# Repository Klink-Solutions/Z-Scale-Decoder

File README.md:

# Z-Scale-Decoder

### A ultra tiny DCC decoder build for Z scale trains using the universal DCC protocoll at 10V

## Why this exists
All Z-scale trains on the market today are analog meaning they have poor slow speed performance as the motor jolts to life to get it going. They are also limited to only 1 train per track loop.
My DCC decoder is meant to bridge this gap and fit in larger locomotives and the Rokuhan® "Shorties" carriages to allow for precise pwm motor control with back EMF detection, multiple trains per loop, and optional rgb LED for dynamic running lights.  

## What it does

* ATtiny826 8-bit AVR MCU base running a DCC decoder
* Runs straight from DCC track power, up to 10 V
* Bridge rectifier, (So it works with either track polarity)
* DRV8220 H-bridge motor driver for high compatibility
* Back-EMF speed regulation 
* Optional directional front and rear lights plus an optional cab light
* TPS70950 5 V LDO 
* UPDI programming pads  
* 12 x 7.5 mm
* 2-layer board,0201 componets

## Version History
* 0.1
    * Initial release 

## BOM
|Value         |Designator |Footprint     |JLCPCB Part #          |
|--------------|-----------|--------------|-----------------------|
|0.1uF         |C1,C3      |C0201         |C2158829               |
|10uF 25V      |C2         |C1206         |C2158829               |
|2.2uF         |C4         |C0201         |C6204143               |
|1uF           |C5         |C0201         |C307385                |
|PMEG3010AESBYL|D1,D2,D3,D4|D0402         |C28646369              |
|220k          |R1         |R0201         |C158699                |
|470           |R2         |R0201         |C144816                |
|47k           |R3,R5      |R0201         |C100140                |
|22k           |R4,R6      |R0201         |C295842                |
|DRV8220DSGR   |U1         |WSON-8(2x2)   |C3681269               |
|TPS70950DRVR  |U2         |WSON-6-EP(2x2)|C527527                |
|ATTINY826-MU  |U3         |VQFN-20(3x3)  |C3216887               |

## Help

Contact author 

## Author

Lucas Klemmer  
klinksolutions22@gmail.com

## License
MIT LIcense

If anyone ends up reproducing this device or making it even bettter I would be happy to see your improvements and add them to the oficial release.

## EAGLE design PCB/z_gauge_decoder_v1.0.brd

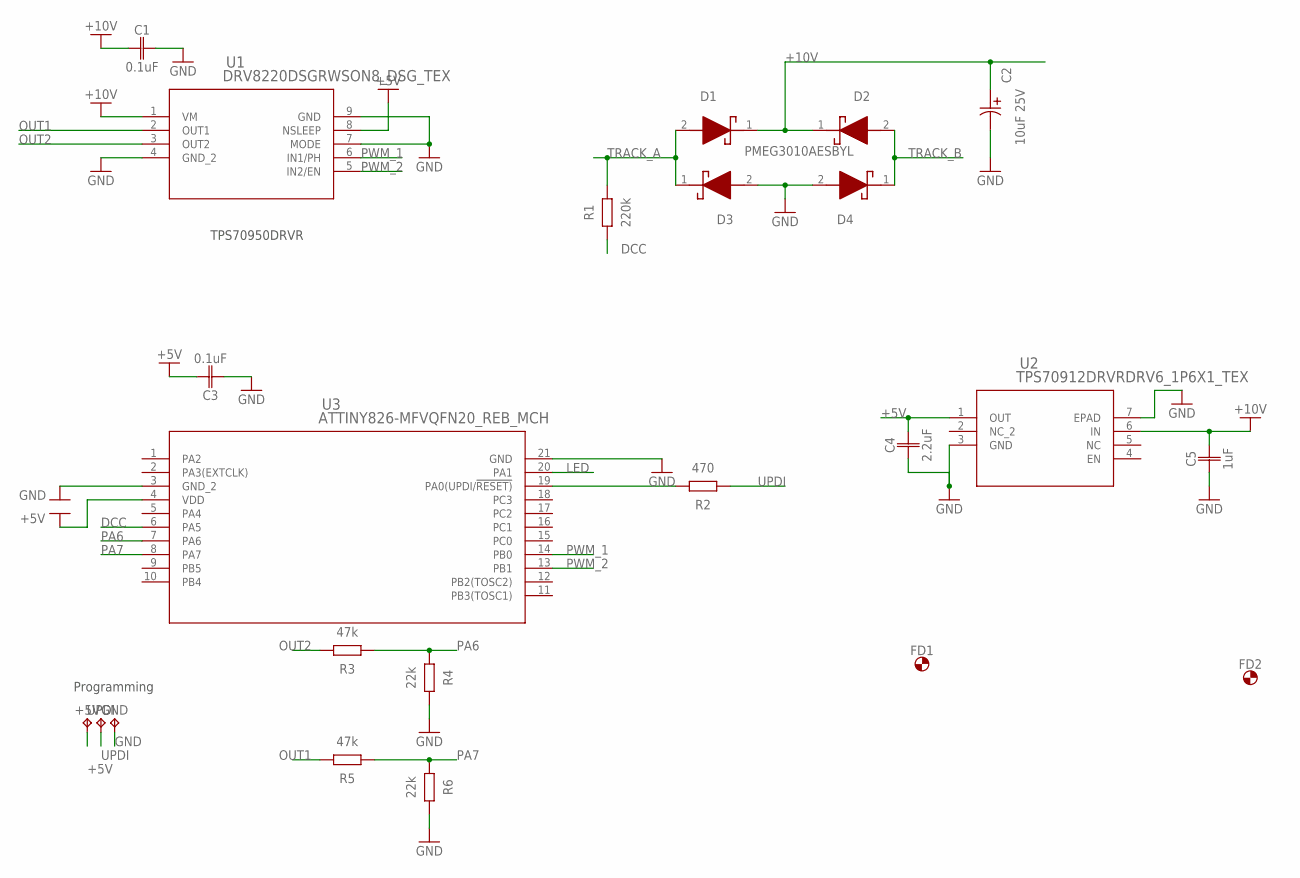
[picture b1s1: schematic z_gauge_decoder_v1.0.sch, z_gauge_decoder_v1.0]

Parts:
+5V: TPTP127R; TP127R
C1, C3: 0.1uF; WE-MK_0201; MPN GRM033R61E104KE14D
C2: 10uF 25V; TAJA_AVX; MPN TCJA106M025R0150E
C4: 2.2uF; WE-MK_0201
C5: 1uF; WE-MK_0201
D1, D2, D3, D4: PMEG3010AESBYL
FD1, FD2: FID_1MM_P
GND: TPTP127R; TP127R
R1: 220k; WCAP-CSGP_0201_H0.3
R2: 470; WCAP-CSGP_0201_H0.3
R3, R5: 47k; WCAP-CSGP_0201_H0.3
R4, R6: 22k; WCAP-CSGP_0201_H0.3
U1: DRV8220DSGRWSON8_DSG_TEX; WSON8_DSG_TEX
U2: TPS70912DRVRDRV6_1P6X1_TEX; DRV6_1P6X1_TEX
U3: ATTINY826-MFVQFN20_REB_MCH; VQFN20_REB_MCH
UPDI: TPTP127R; TP127R

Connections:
+5V: +5V.TP, C3.2, C4.2, U1.8 (NSLEEP), U2.1 (OUT), U3.4 (VDD)
+10V: C1.1, C2.1, C5.2, D1.1 (K), D2.1 (K), U1.1 (VM), U2.6 (IN)
DCC: R1.1, U3.6 (PA5)
GND: C1.2, C2.2, C3.1, C4.1, C5.1, D3.2 (A), D4.2 (A), GND.TP, R4.2, R6.2, U1.4 (GND_2), U1.7 (MODE), U1.9 (GND), U2.3 (GND), U2.7 (EPAD), U3.3 (GND_2), U3.21 (GND)
LED: U3.20 (PA1)
unnamed: R2.2, U3.19 (PA0(UPDI/!RESET))
OUT1: R5.2, U1.2 (OUT1)
OUT2: R3.2, U1.3 (OUT2)
PA6: R3.1, R4.1, U3.7 (PA6)
PA7: R5.1, R6.1, U3.8 (PA7)
PWM_1: U1.6 (IN1/PH), U3.14 (PB0)
PWM_2: U1.5 (IN2/EN), U3.13 (PB1)
TRACK_A: D1.2 (A), D3.1 (K), R1.2
TRACK_B: D2.2 (A), D4.1 (K)
UPDI: R2.1, UPDI.TP

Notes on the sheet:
TPS70950DRVR
Programming

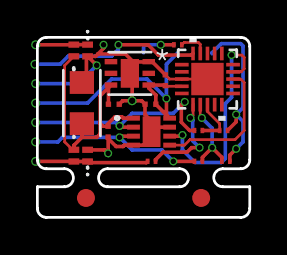
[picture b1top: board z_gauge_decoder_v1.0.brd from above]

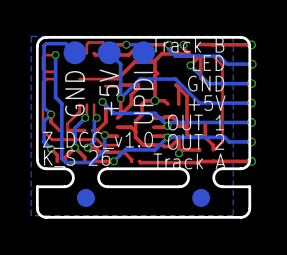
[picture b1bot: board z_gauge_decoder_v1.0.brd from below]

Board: 2 copper layers, 11.8 x 10.0 mm, 23 parts (3 on the bottom side), 14 nets.

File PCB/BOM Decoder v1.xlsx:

Comment | Designator | Footprint | JLCPCB Part #（optional）
0.1uF | C1,C3 | C0201 | C2158829
10uF 25V | C2 | C1206 | C2158829
2.2uF | C4 | C0201 | C6204143
1uF | C5 | C0201 | C307385
PMEG3010AESBYL | D1,D2,D3,D4 | D0402 | C28646369
220k | R1 | R0201 | C158699
470 | R2 | R0201 | C144816
47k | R3,R5 | R0201 | C100140
22k | R4,R6 | R0201 | C295842
DRV8220DSGR | U1 | WSON-8(2x2) | C3681269
TPS70950DRVR | U2 | WSON-6-EP(2x2) | C527527
ATTINY826-MU | U3 | VQFN-20(3x3) | C3216887

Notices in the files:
parts and their libraries:
COPYRIGHT: Copyright (C) 2026 Ultra Librarian. All rights reserved.
